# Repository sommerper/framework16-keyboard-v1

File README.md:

# Framework 16 Keyboard v1

Here's an ortholinear split keyboard that fits in your Framework 16 instead of the default keyboard.

It's using Kaihl Choc switches and the case has an angle of 5 degrees so it will not allow you to close the laptop while using it.

## ZMK and QMK

There some settings for zmk and qmk to get you started with the correct pin layout. The ZMK config is based on [Urob's config](https://github.com/urob/zmk-config)

Any Pro Micro compatible controller should work. The nice!nano v2 is used in the image, and I have also connected an RP2040 without any problems. 

## 3D Print Files
- Left and Right are for the laptop. They should have a tight fit without having to squeeze them in between the other components. 
- Bottom is for your desk so you can choose to put the pcb on your desk as well. It's possible to fit this on the build plate of a standard Prusa mk3s if you put it diagonally.
- Top is for travel protection. It fits on top of the Bottom case with the keyboard inside.

## ⚠️ Disclaimer

These PCB files are provided **as-is**, without any warranty or guarantee of functionality or safety. Use them at your own risk. I am not responsible for any damage, injury, or loss resulting from the use of these files.

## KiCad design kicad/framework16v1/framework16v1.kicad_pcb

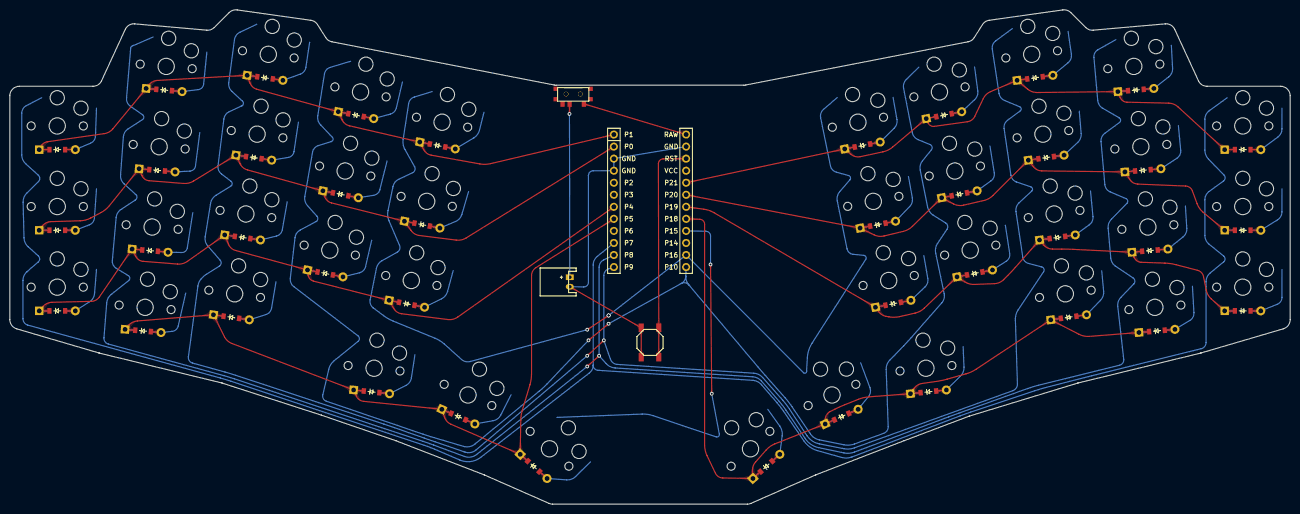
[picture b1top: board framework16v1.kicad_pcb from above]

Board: 2 copper layers, 270.0 x 104.2 mm, 84 parts (0 on the bottom side), 58 nets.

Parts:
B1: SW_TACT_ALPS_SKQGABE010
D1, D2, D3, D4, D5, D6, D7, D8, D9, D10, D11, D12, D13, D14, D15, D16, D17, D18, D19, D20, D21, D22, D23, D24, D25, D26, D27, D28, D29, D30, D31, D32, D33, D34, D35, D36, D37, D38, D39, D40: ComboDiode
JST1: JST_PH_S2B-PH-K_02x2.00mm_Angled
MCU1: mcu_supermini_nrf52840
S1, S2, S3, S4, S5, S6, S7, S8, S9, S10, S11, S12, S13, S14, S15, S16, S17, S18, S19, S20, S21, S22, S23, S24, S25, S26, S27, S28, S29, S30, S31, S32, S33, S34, S35, S36, S37, S38, S39, S40: PG1350
T1: SPDT_C128955

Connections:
BAT: JST1.1, T1.2
GND: B1.1, JST1.2, MCU1.2, MCU1.21, MCU1.22
P0: D2.1, D6.1, D10.1, D13.1, D16.1, MCU1.23
P1: D3.1, D7.1, D11.1, D14.1, D17.1, MCU1.24
P4: D1.1, D5.1, D9.1, D12.1, D15.1, MCU1.18
P5: D4.1, D8.1, D18.1, D19.1, D20.1, MCU1.17
P7: MCU1.15, S1.1, S2.1, S3.1, S21.1, S22.1, S23.1
P8: MCU1.14, S4.1, S5.1, S6.1, S7.1, S24.1, S25.1, S26.1, S27.1
P9: MCU1.13, S8.1, S9.1, S10.1, S11.1, S28.1, S29.1, S30.1, S31.1
P10: MCU1.12, S12.1, S13.1, S14.1, S18.1, S32.1, S33.1, S34.1, S38.1
P15: MCU1.9, S20.1, S40.1
P16: MCU1.11, S15.1, S16.1, S17.1, S19.1, S35.1, S36.1, S37.1, S39.1
P18: D24.1, D28.1, D38.1, D39.1, D40.1, MCU1.8
P19: D21.1, D25.1, D29.1, D32.1, D35.1, MCU1.7
P20: D22.1, D26.1, D30.1, D33.1, D36.1, MCU1.6
P21: D23.1, D27.1, D31.1, D34.1, D37.1, MCU1.5
RAW: MCU1.1, T1.1
RST: B1.2, MCU1.3
far_thumb: D20.2, S20.2
home_thumb: D19.2, S19.2
index_home: D12.2, S12.2
index_num: D14.2, S14.2
index_top: D13.2, S13.2
inner_home: D15.2, S15.2
inner_num: D17.2, S17.2
inner_top: D16.2, S16.2
middle_bottom: D8.2, S8.2
middle_home: D9.2, S9.2
middle_num: D11.2, S11.2
middle_top: D10.2, S10.2
mirror_far_thumb: D40.2, S40.2
mirror_home_thumb: D39.2, S39.2
mirror_index_home: D32.2, S32.2
mirror_index_num: D34.2, S34.2
mirror_index_top: D33.2, S33.2
mirror_inner_home: D35.2, S35.2
mirror_inner_num: D37.2, S37.2
mirror_inner_top: D36.2, S36.2
mirror_middle_bottom: D28.2, S28.2
mirror_middle_home: D29.2, S29.2
mirror_middle_num: D31.2, S31.2
mirror_middle_top: D30.2, S30.2
mirror_near_thumb: D38.2, S38.2
mirror_pinky_home: D21.2, S21.2
mirror_pinky_num: D23.2, S23.2
mirror_pinky_top: D22.2, S22.2
mirror_ring_bottom: D24.2, S24.2
mirror_ring_home: D25.2, S25.2
mirror_ring_num: D27.2, S27.2
mirror_ring_top: D26.2, S26.2
near_thumb: D18.2, S18.2
pinky_home: D1.2, S1.2
pinky_num: D3.2, S3.2
pinky_top: D2.2, S2.2
ring_bottom: D4.2, S4.2
ring_home: D5.2, S5.2
ring_num: D7.2, S7.2
ring_top: D6.2, S6.2

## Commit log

2025-04-08 case
2025-04-08 rename files
2025-04-08 zmk config
2025-04-08 qmk config
2025-04-08 kicad
2025-04-08 readme
